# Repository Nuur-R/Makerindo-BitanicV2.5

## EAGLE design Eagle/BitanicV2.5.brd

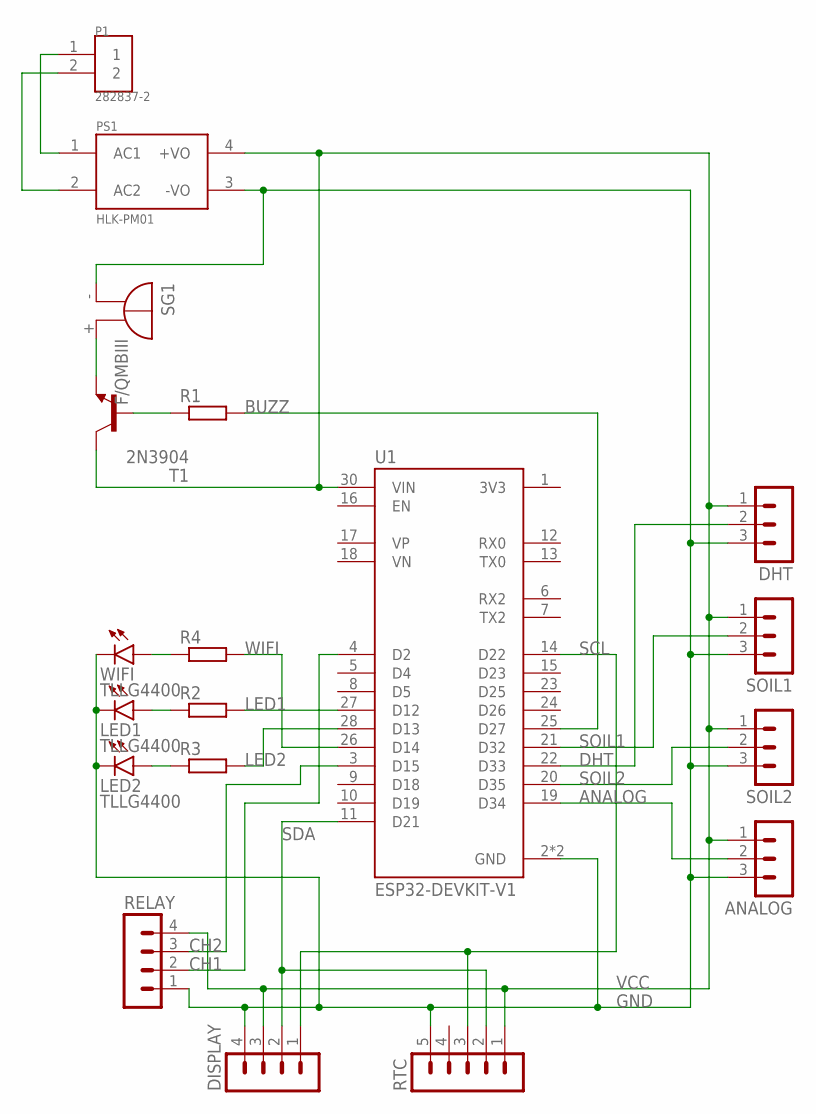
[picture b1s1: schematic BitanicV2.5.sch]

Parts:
ANALOG: MA03-1
DHT: MA03-1
DISPLAY: MA04-1
LED1, LED2: TLLG4400; LED3MM
P1: 282837-2; TE_282837-2
PS1: HLK-PM01; CONV_HLK-PM01
R1, R2, R3, R4: R-EU_0309/12; 0309/12
RELAY: MA04-1
RTC: MA05-1
SG1: F/QMBIII
SOIL1, SOIL2: MA03-1
T1: 2N3904; TO92
U1: ESP32-DEVKIT-V1; MODULE_ESP32_DEVKIT_V1
WIFI: TLLG4400; LED3MM

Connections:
ANALOG: ANALOG.2, U1.19 (D34)
BUZZ: R1.2, U1.25 (D27)
CH1: RELAY.2, U1.4 (D2)
CH2: RELAY.3, U1.3 (D15)
DHT: DHT.2, U1.22 (D33)
GND: ANALOG.3, DHT.3, DISPLAY.4, LED1.K (C), LED2.K (C), PS1.3 (-VO), RELAY.1, RTC.5, SG1.- (+), SOIL1.3, SOIL2.3, U1.2 (GND), U1.29 (GND), WIFI.K (C)
LED1: R2.2, U1.27 (D12)
LED2: R3.2, U1.28 (D13)
unnamed: P1.2, PS1.2 (AC2)
unnamed: P1.1, PS1.1 (AC1)
unnamed: LED2.A, R3.1
unnamed: LED1.A, R2.1
unnamed: R4.1, WIFI.A
unnamed: R1.1, T1.2 (B)
unnamed: SG1.+ (-), T1.3 (E)
SCL: DISPLAY.1, RTC.3, U1.14 (D22)
SDA: DISPLAY.2, RTC.2, U1.11 (D21)
SOIL1: SOIL1.2, U1.21 (D32)
SOIL2: SOIL2.2, U1.20 (D35)
VCC: ANALOG.1, DHT.1, DISPLAY.3, PS1.4 (+VO), RELAY.4, RTC.1, SOIL1.1, SOIL2.1, T1.1 (C), U1.30 (VIN)
WIFI: R4.2, U1.26 (D14)

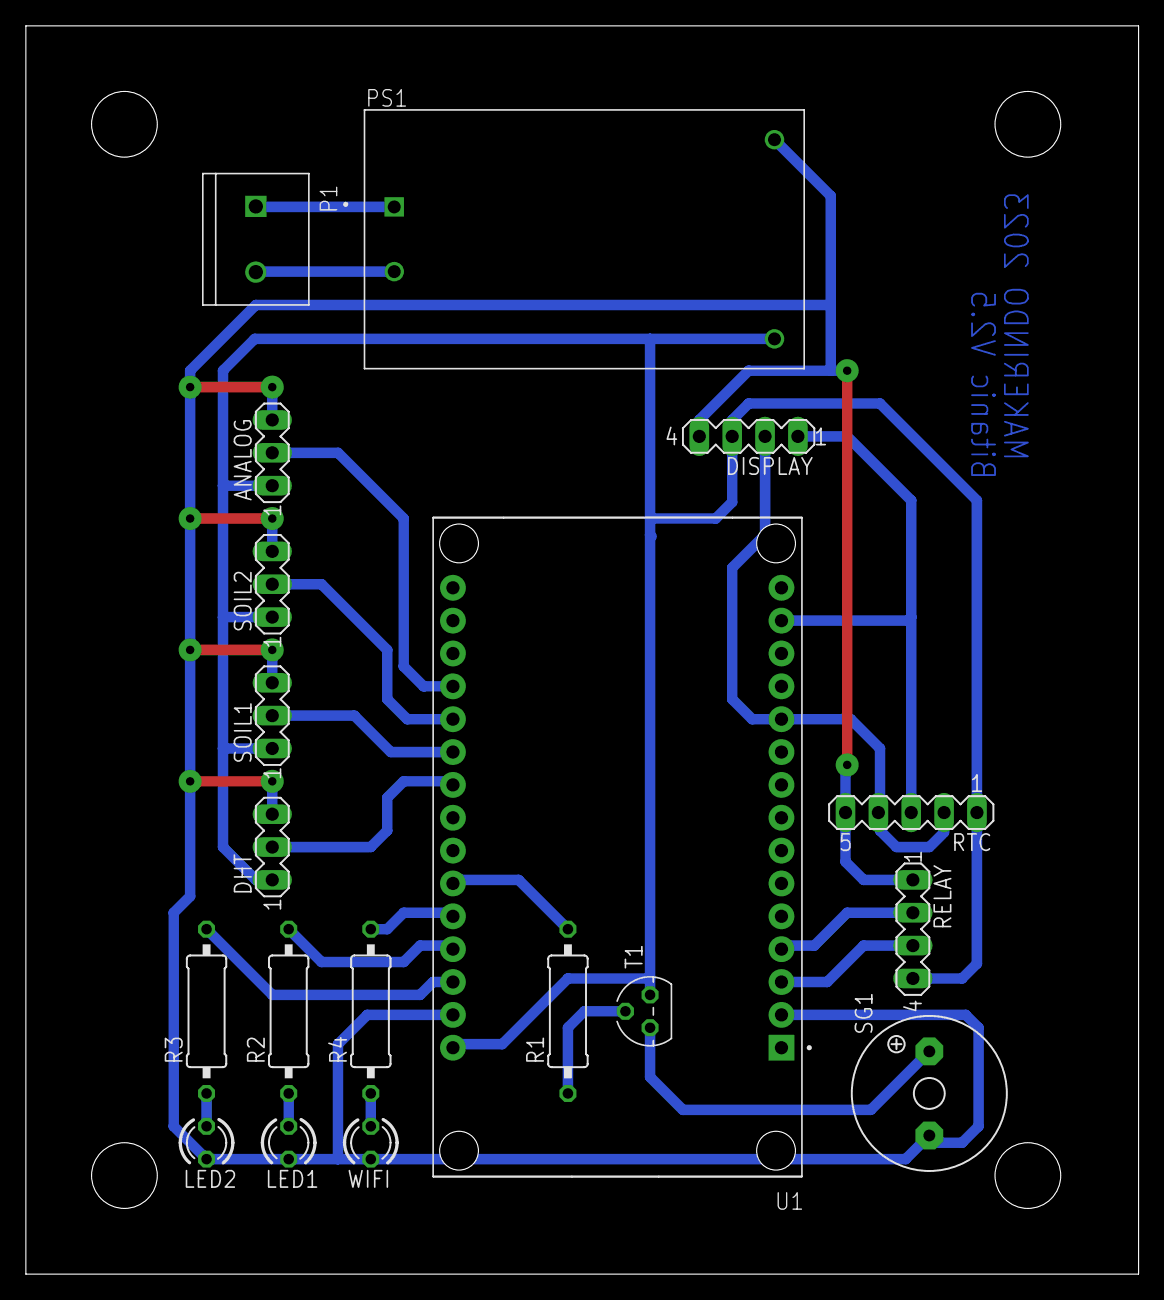
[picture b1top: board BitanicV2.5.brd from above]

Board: 2 copper layers, 86.0 x 96.5 mm, 19 parts (0 on the bottom side), 21 nets.

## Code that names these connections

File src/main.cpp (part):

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#define soilMoisture2 32
#define analogPin 34

#define led1 12
#define led2 13
#define ledWiFi 11
// #define SCREEN_WIDTH 128
// #define SCREEN_HEIGHT 64
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RTC_DS1307 rtc;
// WiFiClient espClient;
// PubSubClient client(espClient);
DHT dht(DHTPIN1, DHTTYPE);
// DHT dht2(DHTPIN2, DHTTYPE);

int Detik, PortValue, countWifi, count2, State1, GlobalCount, h1, h2, LockTime, CountTime, CountMotor, TimeMotor, CountMinggu, TotalMinggu, OnDay, SaveOn, CountDayOn, countEND;
float t1, t2;
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
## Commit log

2023-02-28 pin ok keknya
2023-02-28 Start
